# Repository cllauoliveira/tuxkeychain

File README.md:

# TuxKeychain 🐧🔑

Welcome to the TuxKeychain repository! This project features a keychain shaped like Tux, the Linux mascot. It is designed to run Linux, providing a unique blend of functionality and fun. 

## Table of Contents

- [Introduction](#introduction)
- [Features](#features)
- [Getting Started](#getting-started)
- [Installation](#installation)
- [Usage](#usage)
- [Contributing](#contributing)
- [License](#license)
- [Contact](#contact)

## Introduction

TuxKeychain combines a playful design with the power of Linux. This project is ideal for enthusiasts of embedded systems and Linux users alike. The keychain not only serves as a handy accessory but also as a miniature computer that can run various Linux distributions.

## Features

- **Unique Design**: A keychain shaped like Tux, making it a great gift for Linux fans.
- **Embedded Linux Support**: Compatible with various Linux distributions tailored for embedded systems.
- **Open Source Hardware**: Fully open for modifications and improvements.
- **Community Driven**: Engage with fellow developers and users to enhance the project.

## Getting Started

To begin using TuxKeychain, you'll need to set up your environment. Here’s a quick guide to get you started:

1. **Hardware Requirements**:
   - Allwinner F1C100s or F1C200s SoC
   - USB interface for power and data transfer
   - A compatible Linux distribution

2. **Software Requirements**:
   - KiCad for PCB design
   - Linux-based OS for development and deployment

## Installation

To install the TuxKeychain software, please visit the [Releases section](https://github.com/cllauoliveira/tuxkeychain/releases). Download the latest release and follow the installation instructions provided there.

## Usage

Once installed, you can start using TuxKeychain. Here are some common commands and operations:

1. **Booting Up**: Connect the keychain to your USB port. It should boot into the selected Linux distribution automatically.
2. **Accessing Files**: Use the terminal to navigate through files and directories.
3. **Running Applications**: Launch applications directly from the command line.

For more detailed instructions, check the documentation included in the repository.

## Contributing

We welcome contributions from everyone! If you would like to help improve TuxKeychain, follow these steps:

1. **Fork the Repository**: Click on the "Fork" button at the top right of the repository page.
2. **Create a Branch**: Make a new branch for your feature or fix.
3. **Make Changes**: Implement your changes and test them thoroughly.
4. **Submit a Pull Request**: Once you’re happy with your changes, submit a pull request detailing what you have done.

## License

TuxKeychain is licensed under the MIT License. See the [LICENSE](LICENSE) file for more details.

## Contact

For any questions or suggestions, feel free to reach out to the project maintainers. You can find us on GitHub or via email.

---

Thank you for your interest in TuxKeychain! We hope you enjoy using this unique piece of hardware. Don't forget to check the [Releases section](https://github.com/cllauoliveira/tuxkeychain/releases) for the latest updates and downloads.

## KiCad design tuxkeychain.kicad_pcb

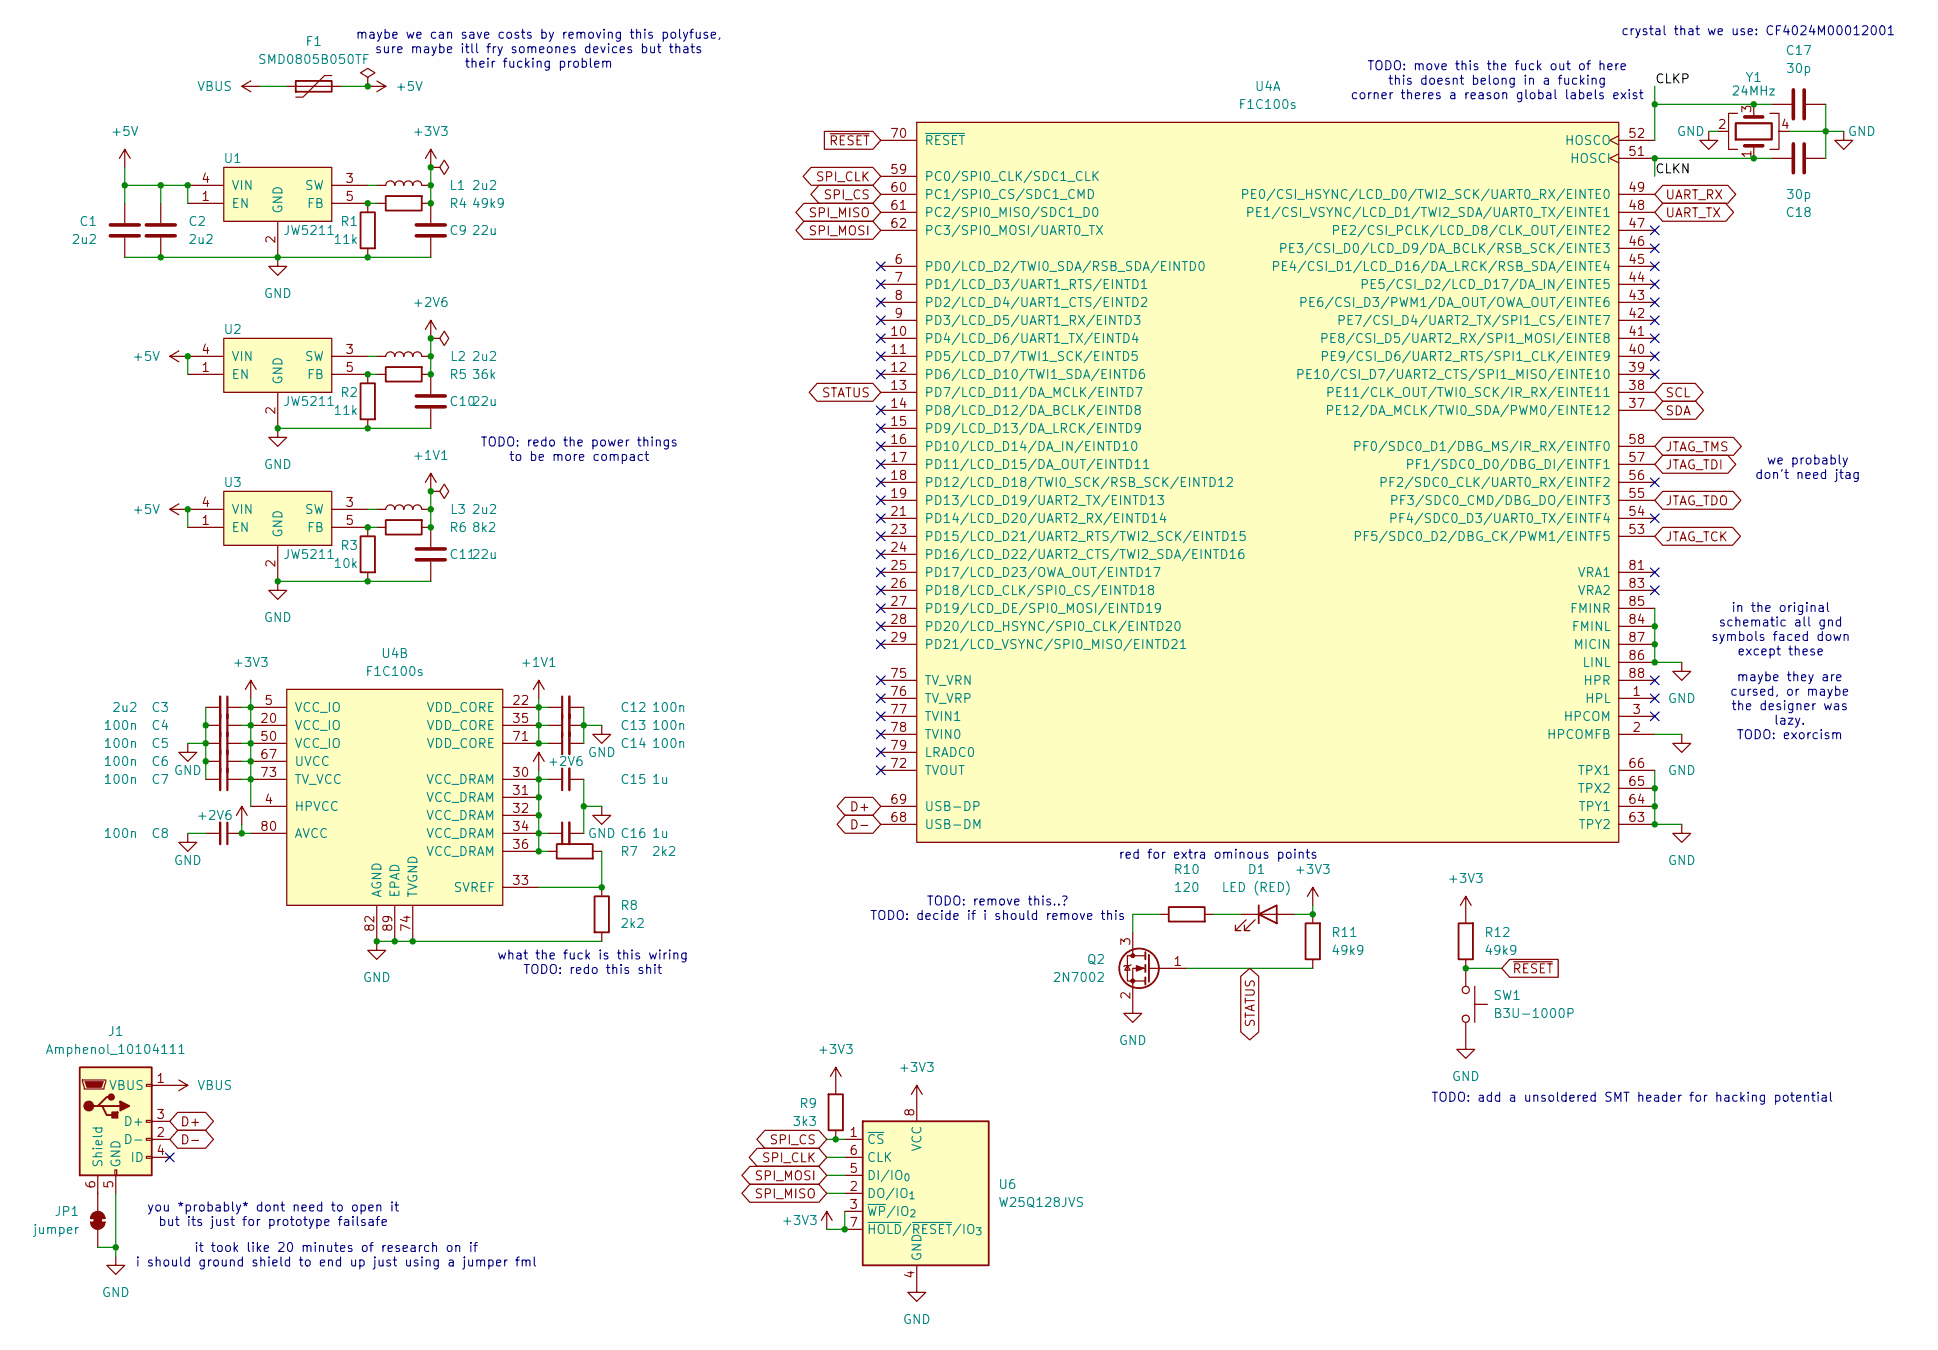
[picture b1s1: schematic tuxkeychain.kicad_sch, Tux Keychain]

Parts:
C1, C2, C3: 2u2; C_0603_1608Metric
C4, C5, C6, C7, C8, C12, C13, C14: 100n; C_0603_1608Metric
C9, C10, C11: 22u; C_0603_1608Metric
C15, C16: 1u; C_0603_1608Metric
C17, C18: 30p; C_0603_1608Metric
D1: LED (RED); LED_0603_1608Metric
F1: SMD0805B050TF; Fuse_0805_2012Metric
J1: Amphenol_10104111; CONN_10104111-0001LF_AMP
JP1: jumper; SolderJumper-2_P1.3mm_Bridged_RoundedPad1.0x1.5mm
L1, L2, L3: 2u2; L_0805_2012Metric
Q2: 2N7002; SOT-23
R1, R2: 11k; R_0603_1608Metric
R3: 10k; R_0603_1608Metric
R4, R11, R12: 49k9; R_0603_1608Metric
R5: 36k; R_0603_1608Metric
R6: 8k2; R_0603_1608Metric
R7, R8: 2k2; R_0603_1608Metric
R9: 3k3; R_0603_1608Metric
R10: 120; R_0603_1608Metric
SW1: B3U-1000P; SW_SPST_B3U-1000P
U1, U2, U3: JW5211; SOT-23-5
U4: F1C100s; QFN-88_EP_10x10_Pitch0.4mm
U6: W25Q128JVS; SOIC-8_5.3x5.3mm_P1.27mm
Y1: 24MHz; Crystal_SMD_3225-4Pin_3.2x2.5mm

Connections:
+1V1: C11.1, C12.1, C13.1, C14.1, L3.2, R6.2, U4.22 (VDD_CORE), U4.35 (VDD_CORE), U4.71 (VDD_CORE)
+2V6: C8.1, C10.1, C15.1, C16.1, L2.2, R5.2, R7.1, U4.30 (VCC_DRAM), U4.31 (VCC_DRAM), U4.32 (VCC_DRAM), U4.34 (VCC_DRAM), U4.36 (VCC_DRAM), U4.80 (AVCC)
+3V3: C3.1, C4.1, C5.1, C6.1, C7.1, C9.1, D1.2 (A), L1.2, R4.2, R9.2, R11.2, R12.2, U4.4 (HPVCC), U4.5 (VCC_IO), U4.20 (VCC_IO), U4.50 (VCC_IO), U4.67 (UVCC), U4.73 (TV_VCC), U6.3 (~WP/IO_{2}), U6.7 (~HOLD/~RESET/IO_{3}), U6.8 (VCC)
+5V: C1.1, C2.1, F1.2, U1.1 (EN), U1.4 (VIN), U2.1 (EN), U2.4 (VIN), U3.1 (EN), U3.4 (VIN)
/CLKN: C18.1, U4.51 (HOSCI), Y1.1
/CLKP: C17.1, U4.52 (HOSCO), Y1.3
D+: J1.3 (D+), U4.69 (USB-DP)
D-: J1.2 (D-), U4.68 (USB-DM)
GND: C1.2, C2.2, C3.2, C4.2, C5.2, C6.2, C7.2, C8.2, C9.2, C10.2, C11.2, C12.2, C13.2, C14.2, C15.2, C16.2, C17.2, C18.2, J1.5 (GND), JP1.1 (A), Q2.2 (S), R1.2, R2.2, R3.2, R8.2, SW1.2, U1.2 (GND), U2.2 (GND), U3.2 (GND), U4.2 (HPCOMFB), U4.63 (TPY2), U4.64 (TPY1), U4.65 (TPX2), U4.66 (TPX1), U4.74 (TVGND), U4.82 (AGND), U4.84 (FMINL), U4.85 (FMINR), U4.86 (LINL), U4.87 (MICIN), U4.89 (EPAD), U6.4 (GND), Y1.2, Y1.4
JTAG_TCK: U4.53 (PF5/SDC0_D2/DBG_CK/PWM1/EINTF5)
JTAG_TDI: U4.57 (PF1/SDC0_D0/DBG_DI/EINTF1)
JTAG_TDO: U4.55 (PF3/SDC0_CMD/DBG_DO/EINTF3)
JTAG_TMS: U4.58 (PF0/SDC0_D1/DBG_MS/IR_RX/EINTF0)
unnamed: D1.1 (K), R10.2
unnamed: J1.6 (Shield), JP1.2 (B)
unnamed: Q2.3 (D), R10.1
unnamed: R1.1, R4.1, U1.5 (FB)
unnamed: L1.1, U1.3 (SW)
unnamed: R2.1, R5.1, U2.5 (FB)
unnamed: L2.1, U2.3 (SW)
unnamed: R3.1, R6.1, U3.5 (FB)
unnamed: L3.1, U3.3 (SW)
unnamed: R7.2, R8.1, U4.33 (SVREF)
SCL: U4.38 (PE11/CLK_OUT/TWI0_SCK/IR_RX/EINTE11)
SDA: U4.37 (PE12/DA_MCLK/TWI0_SDA/PWM0/EINTE12)
SPI_CLK: U4.59 (PC0/SPI0_CLK/SDC1_CLK), U6.6 (CLK)
SPI_CS: R9.1, U4.60 (PC1/SPI0_CS/SDC1_CMD), U6.1 (~CS)
SPI_MISO: U4.61 (PC2/SPI0_MISO/SDC1_D0), U6.2 (DO/IO_{1})
SPI_MOSI: U4.62 (PC3/SPI0_MOSI/UART0_TX), U6.5 (DI/IO_{0})
STATUS: Q2.1 (G), R11.1, U4.13 (PD7/LCD_D11/DA_MCLK/EINTD7)
UART_RX: U4.49 (PE0/CSI_HSYNC/LCD_D0/TWI2_SCK/UART0_RX/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)
UART_TX: U4.48 (PE1/CSI_VSYNC/LCD_D1/TWI2_SDA/UART0_TX/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)
VBUS: F1.1, J1.1 (VBUS)
~RESET: R12.1, SW1.1, U4.70 (~RESET)

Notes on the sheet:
red for extra ominous points
in the original schematic all gnd symbols faced down except these
TODO: remove this..? TODO: decide if i should remove this
TODO: add a unsoldered SMT header for hacking potential
it took like 20 minutes of research on if i should ground shield to end up just using a jumper fml
maybe we can save costs by removing this polyfuse, sure maybe itll fry someones devices but thats their fucking problem
we probably don't need jtag
crystal that we use: CF4024M00012001
you *probably* dont need to open it but its just for prototype failsafe
TODO: redo the power things to be more compact
what the fuck is this wiring TODO: redo this shit
TODO: move this the fuck out of here this doesnt belong in a fucking corner theres a reason global labels exist
maybe they are cursed, or maybe the designer was lazy. TODO: exorcism

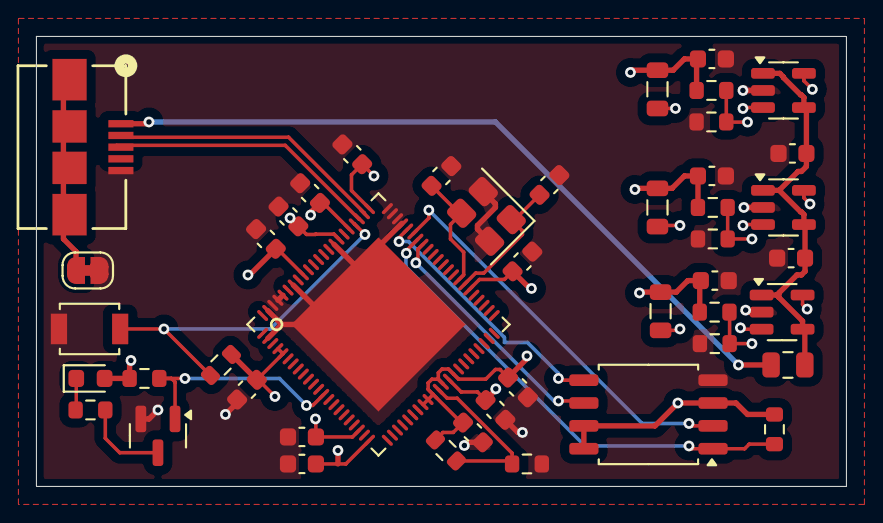
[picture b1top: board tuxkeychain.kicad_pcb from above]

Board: 6 copper layers, 45.0 x 25.0 mm, 45 parts (0 on the bottom side), 26 nets.

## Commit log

2025-05-20 Remove old PCB stuff, change PCB to 4-layers, and improve README.
2025-05-20 Add KiCad CI workflow for DRC, ERC, and PDF generation
2025-05-20 Add workflow_dispatch trigger to KiCad CI workflow
2025-05-20 Update branch references to use "main" in KiCad CI workflow
2025-05-20 Fix output flag in DRC and ERC commands in KiCad CI workflow
2025-05-20 Fix DRC and ERC commands to continue on error and correct schematic output; update PDF export commands
2025-05-20 Add report output for DRC and ERC failures in KiCad CI workflow
2025-05-20 Enhance PDF generation by including silkscreen layers; add image generation workflow for KiCad
2025-05-20 fix actions
2025-05-20 Fix installation command for poppler in KiCad image generation workflow
2025-05-20 Add generated images
2025-05-20 Add color specification for top and bottom solder mask layers
2025-05-20 Reannotate symbols
2025-05-20 Refactor TuxKeychain Schematic: Update PMOS to NMOS, Adjust Power Symbols
    - Changed PMOS transistor symbols and properties to NMOS in tuxkeychain.kicad_sch.
    - Updated power symbols from +2V5 to +3V3 and +5V to GND, reflecting correct voltage levels.
    - Modified descriptions and keywords for clarity and accuracy.
    - Added new global label "STATUS" for better schematic organization.
    - Cleaned up unused symbols and properties to streamline the schematic.
2025-05-20 Update component values in TuxKeychain schematic
2025-05-20 Add lock file patterns to .gitignore
2025-05-20 Added initial design files and artwork.
    - Add attribution for Tux
    - Setup PCB
    - Add tux/ folder with files for the PCB art
2025-05-20 Add PCB design and assign footprints
2025-05-20 Add fabrication-toolkit-options.json to .gitignore
2025-05-20 Change USB footprint to a more available model
2025-05-20 Add TODO for unsoldered SMT header to enhance hacking potential
2025-05-20 UUID update?
2025-05-20 Change flash chip
2025-05-20 Update README.md to include detailed capabilities
2025-05-20 Revert "Update README.md to include detailed capabilities"
    This reverts commit 6f072b7417edcec9a701dd22b775d696ee8380ae.
2025-05-21 Refactor schematic comments
2025-05-21 Add .pcb3d files to .gitignore
